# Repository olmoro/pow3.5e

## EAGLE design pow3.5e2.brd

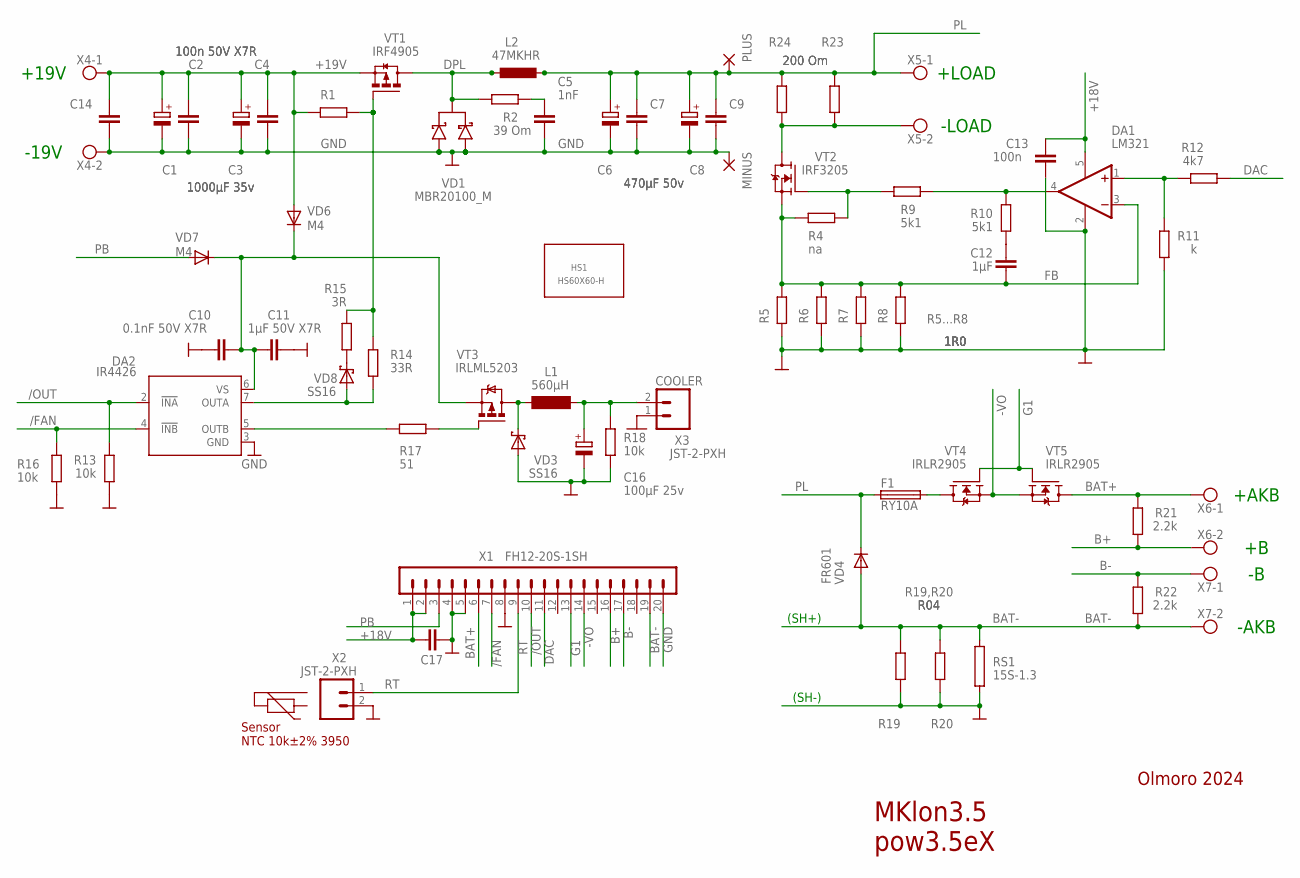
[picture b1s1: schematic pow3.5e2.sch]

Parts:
C1, C3: 1000µF 35v; E5-10,5
C2, C4: 100n 50V X7R; C0805
C5: 1nF; C075-042X103
C6, C8: 470µF 50v; E5-10,5
C7, C9, C14: 1mkF 50V X7R; C0805
C10: 0.1nF 50V X7R; C0805
C11: 1µF 50V X7R; C0805
C12: 1µF; C0805
C13: 100n; C0805
C16: 100µF 25v; E5-6
C17: C-EUC0805; C0805
DA1: LM321; SOT23-5
DA2: IR4426; DIL08
F1: RY10A
HS1: HS60X60-H
L1: 560µH; BS11
L2: 47MKHR
MINUS: 3,81/1,4
PLUS: 3,81/1,4
R1: R-EU_R1206; R1206
R2: 39 Om; 0414/15
R4: na; R1206
R5, R6, R7, R8: 1R0; R2512
R9, R10: 5k1; R0805
R11: k; R0805
R12: 4k7; R0805
R13, R16, R18: 10k; R0805
R14: 33R; R1206
R15: 3R; R1206
R17: 51; R0805
R19, R20: R04; R2512
R21, R22: 2.2k; R1206
R23, R24: 200 Om; 0414/15
RS1: 15S-1.3
VD1: MBR20100_M; TO220DLK
VD3, VD8: SS16; DO214AC
VD4: FR601; DIODE-1_P6-15
VD6, VD7: M4; DO214AC
VT1: IRF4905; TO-220FP_M
VT2: IRF3205; TO-220FP_M
VT3: IRLML5203; MICRO3
VT4, VT5: IRLR2905; TO252
X1: FH12-20S-1SH
X2, X3: JST-2-PXH
X4, X5, X6, X7: AK500/2

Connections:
+18V: C13.2, C17.2, DA1.5 (V+), X1.1, X1.2
+19V: C1.+, C2.2, C3.+, C4.2, C14.1, R1.1, VD6.A, VT1.3 (S), X4.1
-LD: R23.1, R24.1, VT2.2 (D), X5.2
-VO: VT4.3 (S), VT5.3 (S), X1.14
/FAN: DA2.4 (!INB), R16.1, X1.7
/OUT: DA2.2 (!INA), R13.2, X1.10
B+: R21.1, X1.16, X6.2
B-: R22.1, X1.17, X7.1
BAT+: R21.2, VT5.4 (D), X1.6, X6.1
BAT-: R19.1, R20.1, R22.2, RS1.1, VD4.A, X1.19, X7.2
COOLER: C16.+, L1.2, R18.1, X3.2
DAC: R12.2, X1.11
DPL: L2.1, L2.1@2 (1), R2.2, VD1.2 (C), VT1.2 (D)
FB: C12.2, DA1.3 (-IN), R4.1, R5.2, R6.2, R7.2, R8.2, VT2.3 (S)
G1: VT4.1 (G), VT5.1 (G), X1.13
GND: C1.-, C2.1, C3.-, C4.1, C5.2, C6.-, C7.2, C8.-, C9.2, C10.1, C11.1, C13.1, C14.2, C16.-, C17.1, DA1.2 (V-), DA2.3 (GND), MINUS.1, R5.1, R6.1, R7.1, R8.1, R11.2, R13.1, R16.2, R18.2, R19.2, R20.2, RS1.2, VD1.1 (A1), VD1.3 (A2), VD3.A, X1.4, X1.5, X1.8, X1.20, X2.2, X3.1, X4.2
unnamed: DA2.5 (OUTB), R17.2
unnamed: C10.2, C11.2, DA2.6 (VS), VD6.C, VD7.C, VT3.2 (S)
unnamed: R1.2, R14.1, R15.1, VT1.1 (G)
unnamed: R17.1, VT3.1 (G)
unnamed: L1.1, VD3.C, VT3.3 (D)
unnamed: F1.2, VT4.4 (D)
unnamed: DA1.1 (+IN), R11.1, R12.1
unnamed: R4.2, R9.2, VT2.1 (G)
unnamed: R15.2, VD8.C
unnamed: C12.1, R10.2
unnamed: C5.1, R2.1
unnamed: DA2.7 (OUTA), R14.2, VD8.A
PB: VD7.A, X1.3
PL: C6.+, C7.1, C8.+, C9.1, F1.1, L2.2@7 (2), L2.2@8 (2), PLUS.1, R23.2, R24.2, VD4.C, X5.1
RT: X1.9, X2.1
UDAC1: DA1.4 (OUT), R9.1, R10.1

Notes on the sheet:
MKlon3.5 pow3.5eX
Sensor NTC 10k±2% 3950
R5...R8
R19,R20
(SH+)
(SH-)
+AKB
-AKB
+LOAD
-LOAD
+19V
-19V
Olmoro 2024

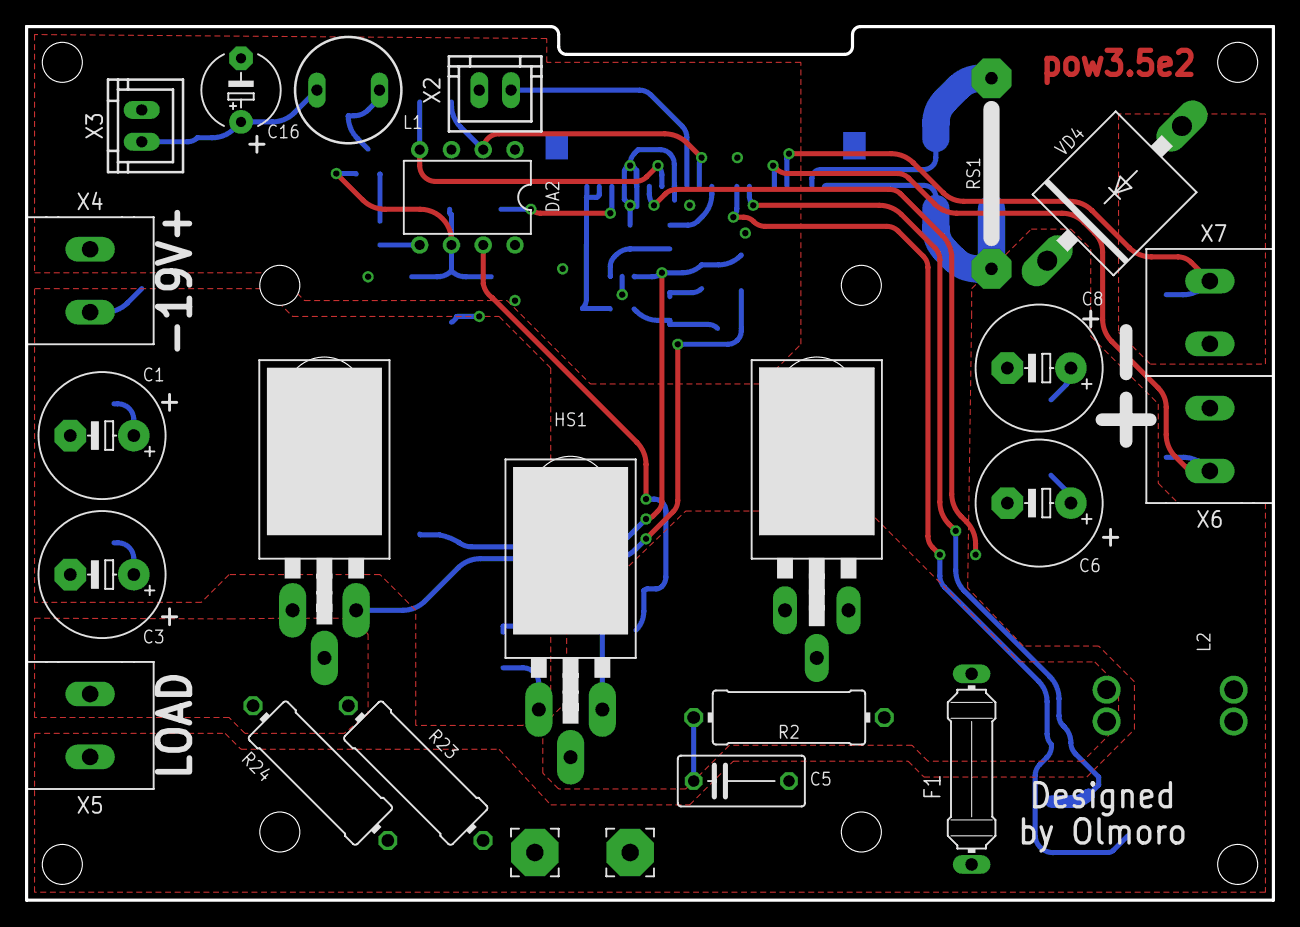
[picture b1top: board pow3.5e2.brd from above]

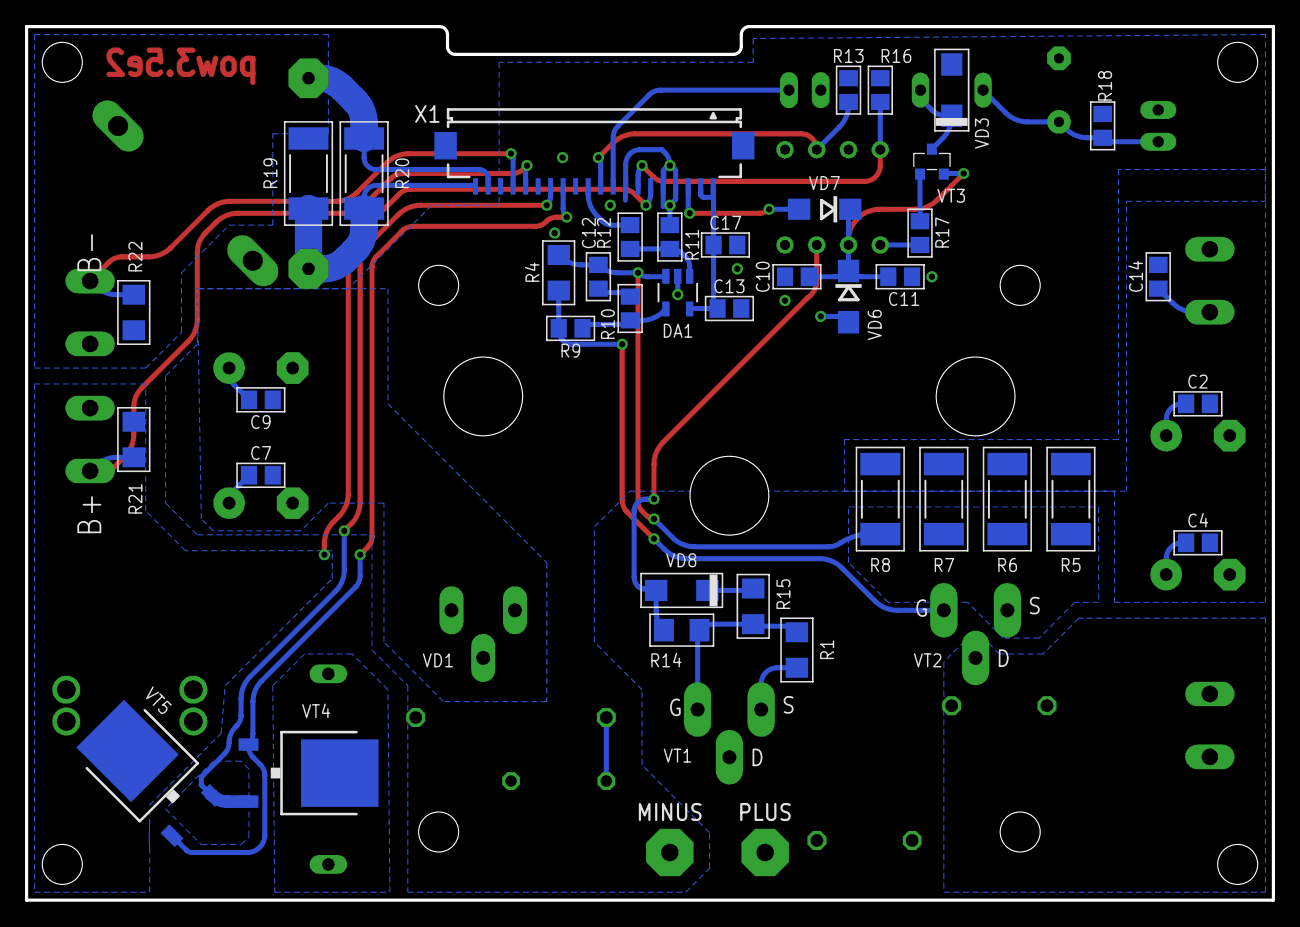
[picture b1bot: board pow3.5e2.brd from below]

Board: 2 copper layers, 99.7 x 69.8 mm, 66 parts (40 on the bottom side), 32 nets.

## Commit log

2024-01-31 gerber
    gerber

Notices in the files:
parts and their libraries:
microbuilder: This work is placed in the public domain, and may be freely used for commercial and non-commercial work with the following conditions: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
